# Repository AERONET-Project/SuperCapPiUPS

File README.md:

# SuperCapPiUPS
 Super capacitor to support rasberry pi graceful shutdown when primary power rail is lost

### Description

This PCB designed to be a hat for rasberry pi; interface on top of a pi. This is a Buck booster. It protects the Pi from crashing when it is unplugged without properly being shut down. There is a lot of open space because I was practicing keeping components as compact as possible. It also leaves a convenient place to put the 15F 5.4V Capacitor. 

### Progress

- [x] Created Symbols for Buck Converter
- [x] Created schematic
- [x] Created footprints for capacitors and Buck Converter and inductor
- [x] Created PCB layout
- [x] put silly images on PCB
- [x] removed silly images on PCB
- [x] Added signiture and USNA crest to PCB
- [x] uploaded to repo
- [ ] finished README

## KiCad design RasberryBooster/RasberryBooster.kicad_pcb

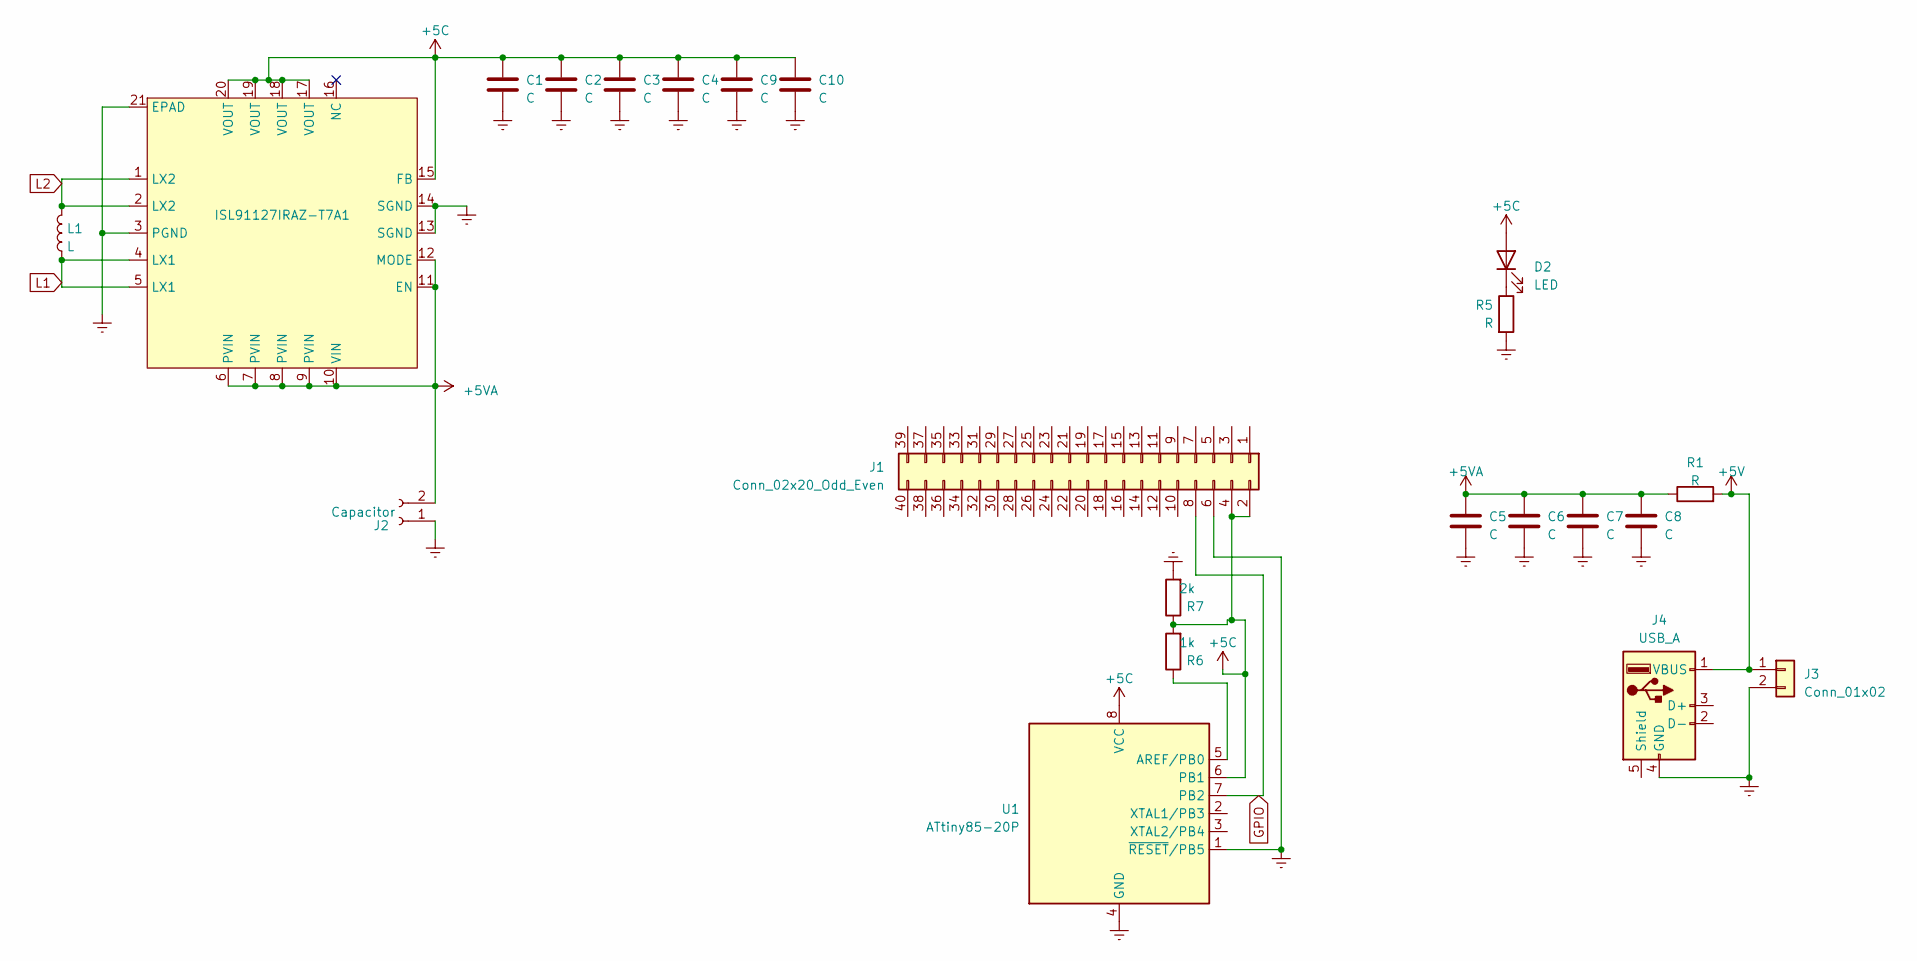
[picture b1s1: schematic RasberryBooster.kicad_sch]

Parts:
C1, C5: C; EEE(Capacitor)
C2, C3, C4, C6, C7, C8, C9, C10: C; C_0603_1608Metric
D2: LED; LED_0603_1608Metric
ISL91127IRAZ-T7A1: ISL91127IRAZ-T7A
J1: Conn_02x20_Odd_Even; PinHeader_2x20_P2.54mm_Vertical
J2: Capacitor; PinSocket_1x02_P2.54mm_Vertical
J3: Conn_01x02; PinSocket_1x02_P2.54mm_Vertical
J4: USB_A; USB_Micro-B_Molex-105017-0001
L1: L; MEKK Inductor
R1, R5: R; R_0603_1608Metric
R6: 1k; R_0603_1608Metric
R7: 2k; R_0603_1608Metric
U1: ATtiny85-20P; DIP-8_W7.62mm

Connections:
+5C: C1.1, C2.1, C3.1, C4.1, C9.1, C10.1, D2.2 (A), ISL91127IRAZ-T7A1.15 (FB), ISL91127IRAZ-T7A1.17 (VOUT), ISL91127IRAZ-T7A1.18 (VOUT), ISL91127IRAZ-T7A1.19 (VOUT), ISL91127IRAZ-T7A1.20 (VOUT), J1.2, J1.4, R6.2, R7.1, U1.6 (PB1), U1.8 (VCC); also elsewhere on the board
+5V: J3.1, J4.1 (VBUS), R1.2
+5VA: C5.1, C6.1, C7.1, C8.1, ISL91127IRAZ-T7A1.6 (PVIN), ISL91127IRAZ-T7A1.7 (PVIN), ISL91127IRAZ-T7A1.8 (PVIN), ISL91127IRAZ-T7A1.9 (PVIN), ISL91127IRAZ-T7A1.10 (VIN), ISL91127IRAZ-T7A1.11 (EN), ISL91127IRAZ-T7A1.12 (MODE), J2.2, R1.1; also elsewhere on the board
Earth: C1.2, C2.2, C3.2, C4.2, C5.2, C6.2, C7.2, C8.2, C9.2, C10.2, ISL91127IRAZ-T7A1.3 (PGND), ISL91127IRAZ-T7A1.13 (SGND), ISL91127IRAZ-T7A1.14 (SGND), ISL91127IRAZ-T7A1.21 (EPAD), J1.6, J2.1, J3.2, J4.4 (GND), R5.2, R7.2, U1.1 (~RESET/PB5), U1.4 (GND); also elsewhere on the board
GPIO: J1.8, U1.7 (PB2)
L1: ISL91127IRAZ-T7A1.4 (LX1), ISL91127IRAZ-T7A1.5 (LX1), L1.1; also elsewhere on the board
L2: ISL91127IRAZ-T7A1.1 (LX2), ISL91127IRAZ-T7A1.2 (LX2), L1.2; also elsewhere on the board
unnamed: D2.1 (K), R5.1
unnamed: R6.1, U1.5 (AREF/PB0)

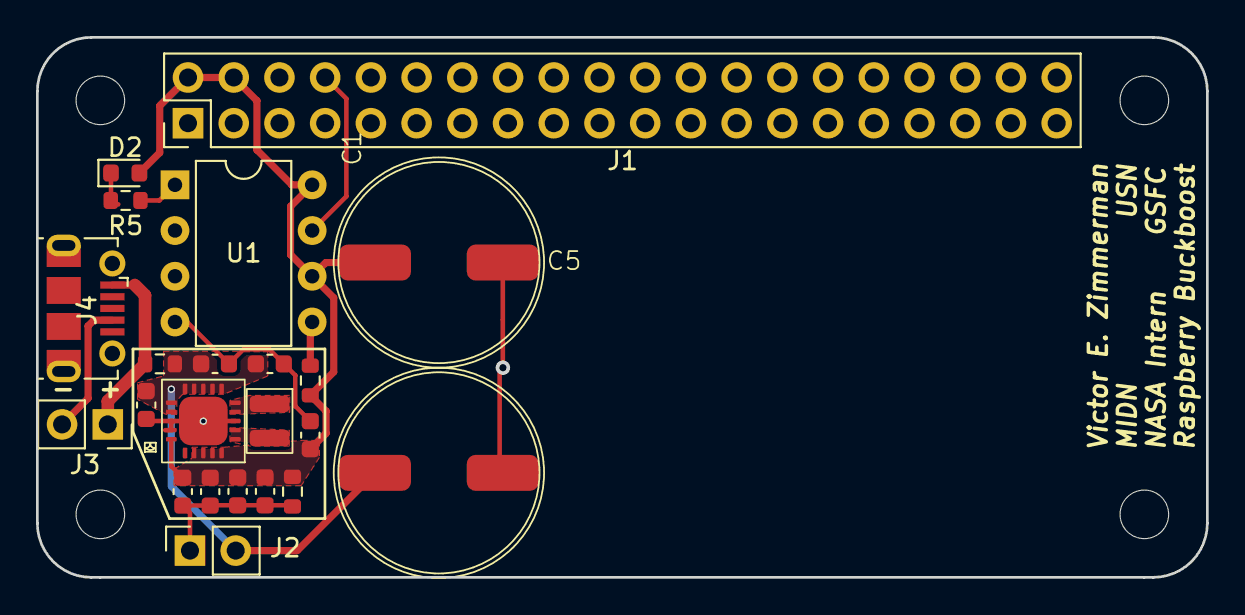
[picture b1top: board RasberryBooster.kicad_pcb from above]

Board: 2 copper layers, 65.0 x 30.0 mm, 22 parts (0 on the bottom side), 9 nets.

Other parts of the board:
ISL: ISL91127IRAZ-T7A

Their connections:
+5C: ISL.15 (FB), ISL.17 (VOUT), ISL.18 (VOUT), ISL.19 (VOUT), ISL.20 (VOUT); also elsewhere on the board
+5VA: ISL.6 (PVIN), ISL.7 (PVIN), ISL.8 (PVIN), ISL.9 (PVIN), ISL.10 (VIN), ISL.11 (EN), ISL.12 (MODE); also elsewhere on the board
Earth: ISL.3 (PGND), ISL.13 (SGND), ISL.14 (SGND), ISL.21 (EPAD); also elsewhere on the board
L1: ISL.4 (LX1), ISL.5 (LX1); also elsewhere on the board
L2: ISL.1 (LX2), ISL.2 (LX2); also elsewhere on the board

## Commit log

2023-06-13 initial upload of super cat
2023-06-15 Finished PCB design
2023-06-15 added readme things
2023-06-15 added PCB Ray-Traced Renders
2023-06-15 added progress to README.md
2023-06-15 corrected title
2023-06-15 added description to README.md
2023-06-15 Added NASA "meatball" and USNA crest to README.md
